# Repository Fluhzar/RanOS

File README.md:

# RanOS

This repository has been moved to [GitLab][0], all further progress will be made there.

[0]: https://gitlab.com/Fluhzar/RanOS

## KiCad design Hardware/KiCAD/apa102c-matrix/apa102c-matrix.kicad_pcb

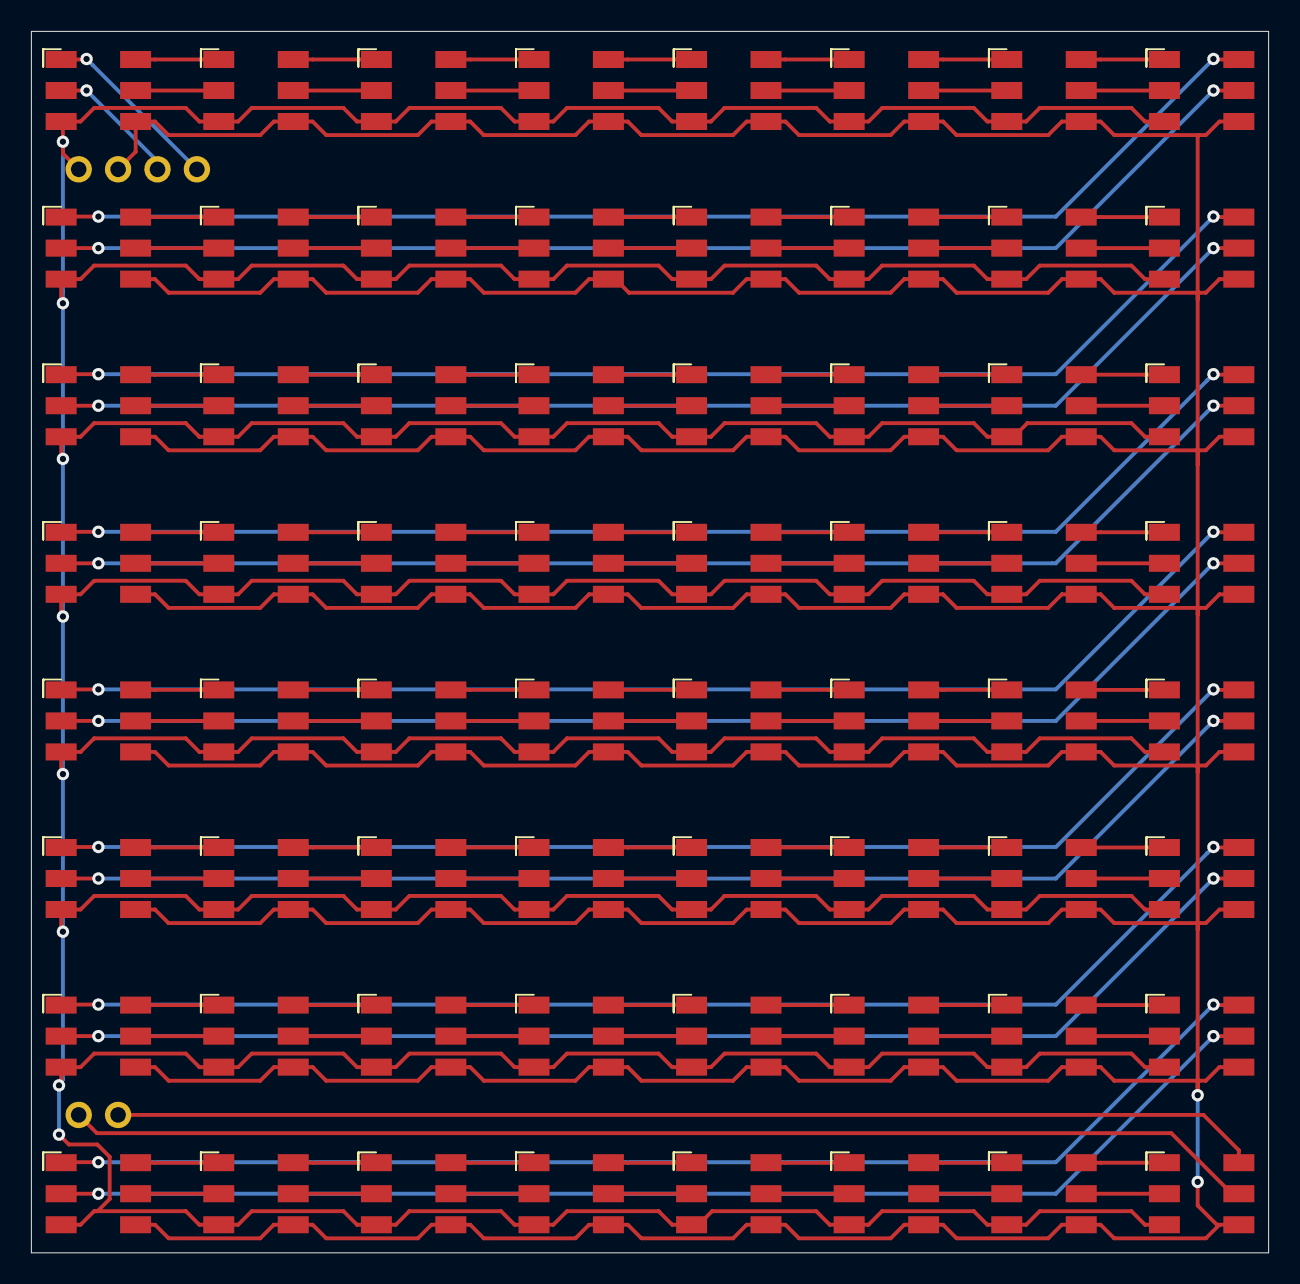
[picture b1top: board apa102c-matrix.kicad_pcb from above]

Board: 2 copper layers, 79.8 x 78.7 mm, 70 parts (0 on the bottom side), 132 nets.

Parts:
D0, D1, D2, D3, D4, D5, D6, D7, D8, D9, D10, D11, D12, D13, D14, D15, D16, D17, D18, D19, D20, D21, D22, D23, D24, D25, D26, D27, D28, D29, D30, D31, D32, D33, D34, D35, D36, D37, D38, D39, D40, D41, D42, D43, D44, D45, D46, D47, D48, D49, D50, D51, D52, D53, D54, D55, D56, D57, D58, D59, D60, D61, D62, D63: APA102-5050
H0, H1, H2, H3, H4, H5: MountingHole_Pad

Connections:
unnamed: D0.1, H3.1
unnamed: D0.2, H2.1
unnamed: D0.3, D1.3, D2.3, D3.3, D4.3, D5.3, D6.3, D7.3, D8.3, D9.3, D10.3, D11.3, D12.3, D13.3, D14.3, D15.3, D16.3, D17.3, D18.3, D19.3, D20.3, D21.3, D22.3, D23.3, D24.3, D25.3, D26.3, D27.3, D28.3, D29.3, D30.3, D31.3, D32.3, D33.3, D34.3, D35.3, D36.3, D37.3, D38.3, D39.3, D40.3, D41.3, D42.3, D43.3, D44.3, D45.3, D46.3, D47.3, D48.3, D49.3, D50.3, D51.3, D52.3, D53.3, D54.3, D55.3, D56.3, D57.3, D58.3, D59.3, D60.3, D61.3, D62.3, D63.3, H0.1
unnamed: D0.4, D1.4, D2.4, D3.4, D4.4, D5.4, D6.4, D7.4, D8.4, D9.4, D10.4, D11.4, D12.4, D13.4, D14.4, D15.4, D16.4, D17.4, D18.4, D19.4, D20.4, D21.4, D22.4, D23.4, D24.4, D25.4, D26.4, D27.4, D28.4, D29.4, D30.4, D31.4, D32.4, D33.4, D34.4, D35.4, D36.4, D37.4, D38.4, D39.4, D40.4, D41.4, D42.4, D43.4, D44.4, D45.4, D46.4, D47.4, D48.4, D49.4, D50.4, D51.4, D52.4, D53.4, D54.4, D55.4, D56.4, D57.4, D58.4, D59.4, D60.4, D61.4, D62.4, D63.4, H1.1
unnamed: D0.5, D1.2
unnamed: D0.6, D1.1
unnamed: D1.5, D2.2
unnamed: D1.6, D2.1
unnamed: D2.5, D3.2
unnamed: D2.6, D3.1
unnamed: D3.5, D4.2
unnamed: D3.6, D4.1
unnamed: D4.5, D5.2
unnamed: D4.6, D5.1
unnamed: D5.5, D6.2
unnamed: D5.6, D6.1
unnamed: D6.5, D7.2
unnamed: D6.6, D7.1
unnamed: D7.5, D8.2
unnamed: D7.6, D8.1
unnamed: D8.5, D9.2
unnamed: D8.6, D9.1
unnamed: D9.6, D10.1
unnamed: D9.5, D10.2
unnamed: D10.5, D11.2
unnamed: D10.6, D11.1
unnamed: D11.5, D12.2
unnamed: D11.6, D12.1
unnamed: D12.5, D13.2
unnamed: D12.6, D13.1
unnamed: D13.5, D14.2
unnamed: D13.6, D14.1
unnamed: D14.5, D15.2
unnamed: D14.6, D15.1
unnamed: D15.5, D16.2
unnamed: D15.6, D16.1
unnamed: D16.5, D17.2
unnamed: D16.6, D17.1
unnamed: D17.5, D18.2
unnamed: D17.6, D18.1
unnamed: D18.5, D19.2
unnamed: D18.6, D19.1
unnamed: D19.5, D20.2
unnamed: D19.6, D20.1
unnamed: D20.5, D21.2
unnamed: D20.6, D21.1
unnamed: D21.5, D22.2
unnamed: D21.6, D22.1
unnamed: D22.5, D23.2
unnamed: D22.6, D23.1
unnamed: D23.5, D24.2
unnamed: D23.6, D24.1
unnamed: D24.5, D25.2
unnamed: D24.6, D25.1
unnamed: D25.5, D26.2
unnamed: D25.6, D26.1
unnamed: D26.5, D27.2
unnamed: D26.6, D27.1
unnamed: D27.5, D28.2
unnamed: D27.6, D28.1
unnamed: D28.5, D29.2
unnamed: D28.6, D29.1
unnamed: D29.5, D30.2
unnamed: D29.6, D30.1
unnamed: D30.5, D31.2
unnamed: D30.6, D31.1
unnamed: D31.5, D32.2
unnamed: D31.6, D32.1
unnamed: D32.5, D33.2
unnamed: D32.6, D33.1
unnamed: D33.5, D34.2
unnamed: D33.6, D34.1
unnamed: D34.5, D35.2
unnamed: D34.6, D35.1
unnamed: D35.5, D36.2
unnamed: D35.6, D36.1
unnamed: D36.5, D37.2
unnamed: D36.6, D37.1
unnamed: D37.5, D38.2
unnamed: D37.6, D38.1
unnamed: D38.5, D39.2
unnamed: D38.6, D39.1
unnamed: D39.5, D40.2
unnamed: D39.6, D40.1
unnamed: D40.5, D41.2
unnamed: D40.6, D41.1
unnamed: D41.5, D42.2
unnamed: D41.6, D42.1
unnamed: D42.5, D43.2
unnamed: D42.6, D43.1
unnamed: D43.5, D44.2
unnamed: D43.6, D44.1
unnamed: D44.5, D45.2
unnamed: D44.6, D45.1
unnamed: D45.5, D46.2
unnamed: D45.6, D46.1
unnamed: D46.5, D47.2
unnamed: D46.6, D47.1
unnamed: D47.5, D48.2
unnamed: D47.6, D48.1
unnamed: D48.5, D49.2
unnamed: D48.6, D49.1
unnamed: D49.5, D50.2
unnamed: D49.6, D50.1
unnamed: D50.5, D51.2
unnamed: D50.6, D51.1
unnamed: D51.5, D52.2
unnamed: D51.6, D52.1
unnamed: D52.5, D53.2
unnamed: D52.6, D53.1
unnamed: D53.5, D54.2
unnamed: D53.6, D54.1
unnamed: D54.5, D55.2
unnamed: D54.6, D55.1
unnamed: D55.5, D56.2
unnamed: D55.6, D56.1
unnamed: D56.5, D57.2
unnamed: D56.6, D57.1
unnamed: D57.5, D58.2
unnamed: D57.6, D58.1
unnamed: D58.5, D59.2
unnamed: D58.6, D59.1
unnamed: D59.5, D60.2
unnamed: D59.6, D60.1
unnamed: D60.5, D61.2
unnamed: D60.6, D61.1
unnamed: D61.5, D62.2
unnamed: D61.6, D62.1
unnamed: D62.5, D63.2
unnamed: D62.6, D63.1
unnamed: D63.5, H4.1
unnamed: D63.6, H5.1

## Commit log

2019-09-27 reset
2019-10-02 Updated paths and fixed broken objs
2019-10-03 Added missing header
2019-10-13 Added serial communication test
2019-10-13 Fixing code
2019-10-13 Added changelog for v0.0.1 release
2019-10-14 Updated Serial code, removing multi-threading and cleaning up some functions
2020-01-09 Created gain test project
2020-01-19 smol code updates
2020-01-19 fixed cast
2020-01-19 Added gitignore entries in preperation for rust projects
2020-01-19 Addition of rust gain project
2020-01-19 gitignore update
2020-01-19 upgraded to wav crate
2020-01-20 Gain test woorrrrkkkkksssssssss
2020-05-25 Improved gain code by a lot
2020-05-25 Ran `cargo fmt`
2020-05-25 Changed chunk size and labeled it with a value
2020-05-25 Improved gain one final time
2020-08-01 Added base code for rust
2020-08-01 Implemented SIGINT handling, updated some documentation, ran `cargo fix`
2020-08-02 Updated `RGB` struct
2020-08-02 Added new struct `NullDraw` that doesn't have any form of output.
2020-08-02 Started work on adding tests
2020-08-02 Updated APA102CPiDraw to be compliant with both APA102C and SK9822 LEDs.
2020-08-02 Typo
2020-08-02 Refactor
2020-08-06 Implemented the collections module and the accompanying `SparseVec` type which will be used as a means of representing LEDs and their arbitrary positions for easier animation control.
2020-08-06 Organized and reorganized files and folders, updated `README.md`
2020-08-11 Tested pi_draw cfg feature on Raspberry Pi 4 with LEDs connected to BCM pins as per the code, fixed issues that arose
2020-08-11 Upgraded code with statistics tracking
2020-08-11 Updated documentation comments
2020-08-11 Fixed issue with timer code in unrestricted speed
2020-08-11 Updated code, ran tests, not looking good doc
    Efficiency of code is `O(1/n)`, specifically around `10^5/n + 10^2` (where `n` is the number of LEDs). Refactoring and other code tests will likely help that figure. The code currently runs 256 LEDs 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
2020-08-12 Big refactoring update
2020-08-12 Made nicer terminal output settings.
2020-08-12 Added support for passing in size (number of LEDs) by commandline argument
2020-08-13 Fixed error
2020-08-13 Attempting to parallelize GPIO writes
2020-08-13 Better formatting
2020-08-13 Added PlatformIO project for Teensy using the rust code in `Code/base/` rewritten to C++.
2020-08-14 Code improvements
2020-08-14 Implemented `RGB::into_hsv`
2020-08-14 Moved to smart pointers for safer memory management
2020-08-14 Uncommented statistics printing code.
2020-08-14 Simplified a bit of the run code
2020-08-14 Removed time restriction on stats printing.
2020-08-14 Added strobe effect (commented it out so no one gets surprised by flashing lights that weren't expected).
2020-08-21 Updated rust code from some of the c++ updates and ran `cargo fmt`.
2020-08-21 Moved `util::frame::Frame` to `frame::Frame`.
2020-08-21 Forgot about `null_draw`.
2020-08-21 Created new `ds` module. Moved `collections` module into `ds` module. Moved `RGB` into `ds` module. Moved `Frame` into `collections` module. Added read and write functions to `Frame` and `RGB` to ass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
2020-08-21 cargo fmt
2020-08-21 Added member to `Frame` that expresses self-control over it's own duration it should be displayed for.
2020-08-21 Updated code to match the new `Frame` behavior, and fixed some issues with `bool` not being directly representable as bytes like the other numeric literal types.
2020-09-04 Updated the `DrawStats` struct to track stats by-LED in addition to by-frame
2020-09-04 Updated pins
2020-09-04 Turned the program into an infinite loop that can only be broken out of with SIGINT (ctrl+c).
2020-09-04 Fixed print statemnt
2020-09-05 Set a more eye-friendly brightness.
2020-09-05 Implemented strobe effect
2020-09-06 Documented the `Strobe` struct and methods.
2020-09-06 Implemented some new traits for easier formatting for pretty-printing for terminal outputs, and implemented them for the animations.
2020-09-06 Various minor fixes and improvements
2020-09-06 Added some more functionality to `Info`, making it easier to work with in a more dynamic environment.
2020-09-06 Added custom implementations for `Clone` to be more akin to cloning + resetting the object as I think that will be far more beneficial for this project.
2020-09-06 Some minor refactoring and tweaks.
2020-09-06 Maintain some semblance of grammar.
2020-09-06 Fixed custom `Clone` implementation.
2020-09-07 Implemented `Info` for `Draw`-implementing types, added functions in the `animation` and `draw` module to get info about all their objects for easy pretty-printing.
2020-09-07 Minor `cargo fmt` changes.
2020-09-07 Added safe defaults for the animations
2020-09-07 Changed the module info functions to just return a `Vec` of the info objects themselves instead of trying to do everything at once.
2020-09-07 Added safe defaults for the drawers.
2020-09-07 Modified the drawer result type to return the boxed animations that were ran during the call to run, allowing for easier looping of the whole system.
2020-09-07 Added match functions to the animation and draw module, will be used in the forthcoming command line app interface.
2020-09-07 Removed the features, as the forthcoming command line app will unify a lot of the systems.
2020-09-07 Updated some defaults.
2020-09-07 Implemented the command line app.
2020-09-07 Added CLion IDE config stuffs.
2020-09-07 Improved imports
2020-09-07 Grammar
2020-09-07 Removed CLion IDE config stuffs
2020-09-07 Removed mistakenly-added files
2020-09-08 Added some missing documentation
2020-09-09 Added documentation to the app struct.
2020-09-09 Added new ConstVal type to syntactically represent values that won't be changed during its lifetime.
2020-09-09 Implemented `ConstVal` into the animation types.
2020-09-09 Added a `reset` method to the `Animation` trait, fixing issue with `App` looping animations.
2020-09-09 Refactored code to be more heavily controlled by the `App` struct.
2020-09-27 Moved clear-screen call so that it only occurs if `termdraw` is used
2020-09-27 Implemented brightness command for the app
2020-09-27 Minor refactor/organization of code
2020-09-30 Fixed some grammatical inconsistency and missing help dialog
2020-09-30 Upgrade pi_draw code to be more accurate (and faster thanks to no longer using `RefCell`)
2020-09-30 Added new drawer `SpeedPiDraw` that pseudo-parallelises the writing to gpio pins
2020-10-12 Added conditional formatting to ensure `rppal` code is compiled only on linux systems
2020-10-12 Small refactor
2020-10-12 Some small refactors and implementation of a draw builder notation. Ran `cargo fmt` on the `draw` module.
2020-10-12 Changed builder type
2020-10-12 Integrated builder into the rest of the app structure.
2020-10-15 Implemented new option for controlling frame speed
2020-10-15 A word
2020-10-15 Reorganized code projects, moving old unused stuff to a separate `deprecated` folder
2020-10-15 Organized the hardware folder a bit
2020-10-15 Updated a lot of the terms of the project outline
2020-10-15 Updated ignore bc ew macOS
2020-10-15 Updated readme doc
2020-10-16 Performed a biiiig refactor, moving all of the `base` code into separate projects/crates.
2020-10-16 Some stuff that git thought was a sub-root for some reason, idk
2020-10-16 Fixed a miss-named parameter
2020-10-17 Removed unnecessary includes
2020-10-17 Added new project for upcoming animation editor
2020-10-18 Moved sparse-vector implementation to a different crate to minimize the work on my end
2020-10-21 Changed to accumulating stats over runtime instead of continuous printing
2020-11-15 Amethyst pong tutorial, step 2
2020-11-23 Updated some behavior in `ranos_ds`
2020-11-23 Added new functionality to `ranos_animation`
2020-11-23 Adjusted cycle animation default
2020-11-23 Adjusted cycle default duration to be divisible by 3
2020-11-23 Fixed timing bc I'm a dumbdumb
2020-11-23 Updated some documentation
2020-12-20 Refactoring work
2021-01-04 I know have a fully functioning 64 LEDs on a single board, so need to update the sizes to reflect such
2021-01-05 Big refactor, successfully culling a lot of boiler-plate, still a ways to go.
2021-01-07 Various in-progress changes. Borrow checker givin me a heckin ache in the head
2021-01-08 Fixed implementation issues that blocked me before
2021-01-08 More refactor and SerDe work
2021-01-08 Finished refactoring individual animations
2021-01-08 More serde implementations, next up is the displays
2021-01-08 More modifications to builders
2021-01-10 Added additional requirements for builder for safety
2021-01-10 Added `typetag` dependency, allowing trait objects to be serialized
2021-01-10 Cleaning up documentation
2021-01-10 Some small bug fixing
2021-01-10 Added serialization tests to ranos_draw
2021-01-10 adjusted behavior of tests
2021-01-10 Added tests for remaining serialized items
2021-01-10 Finished last round of testing, added hard-coded usage test in main of ranos_app
2021-01-10 Refactor complete
2021-01-10 Final adjustments
2021-01-10 Final doc changes and dependency checks
2021-01-10 Okay this is actually truly the final touches
2021-01-10 except I forgot to run cargo fmt one last time
2021-01-10 guess what i forgot!
2021-01-10 added additional parameter for pidraw to account for separate hardware brightness and color brightness
2021-01-10 Updated tests to use `ron` instead of `serde_json`
2021-01-10 Added looping support to the display
2021-01-10 Added SIGINT handling back in.
2021-01-12 Implemented tracking through the timer, replacing the `DrawStats` struct.
2021-01-13 Started work on the audio components
2021-01-15 Audio code work
2021-01-16 More audio work
2021-01-16 I'm good at this I swear
2021-01-16 Added simple static solid color "animation"
2021-01-16 Updated doc comments
2021-01-18 Added base additions for new filter object
2021-01-18 Removed duration tracking from animations
2021-01-18 Adjusting API
2021-01-18 Adjusted filter api to match animation api
2021-01-18 Changed animation to generator
2021-01-18 Modified generator and display api
2021-01-18 Updated usage
2021-01-18 Updated tests
2021-01-18 ran cargo fmt
2021-01-18 Finished filter implementation Refactored `Breath` and `Strobe` to be filters.
2021-01-18 I'm good at forgetting things
2021-02-20 Notated removed repo
